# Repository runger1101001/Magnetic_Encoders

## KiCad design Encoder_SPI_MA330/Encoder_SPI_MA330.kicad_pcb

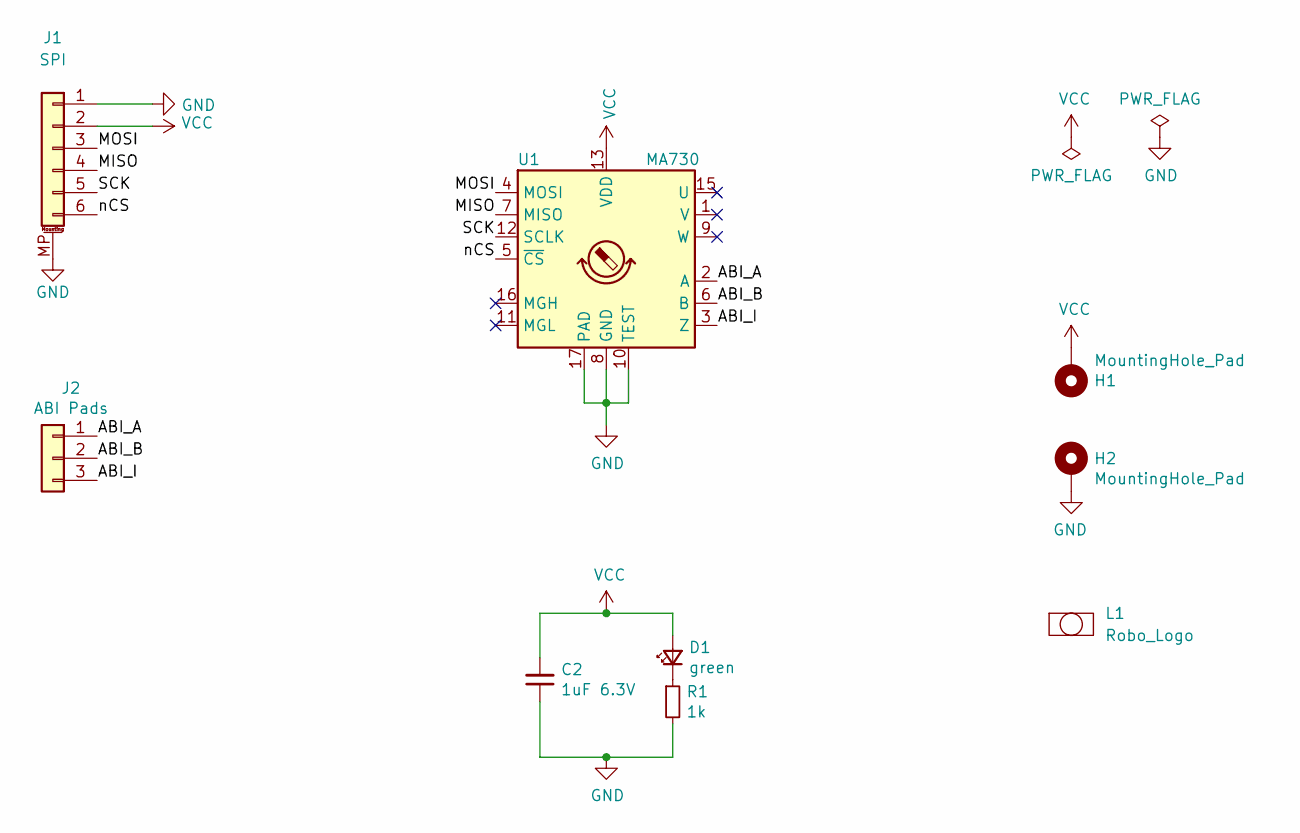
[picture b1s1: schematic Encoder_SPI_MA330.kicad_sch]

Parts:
C2: 1uF 6.3V; C_0402_1005Metric; Part GRT155C80J105KE01D
D1: green; LED_0402_1005Metric; Part 150040VS73240
H1, H2: MountingHole_Pad; MountingHole_2.2mm_M2_ISO7380_Pad
J1: Conn_01x06_MountingPin; JST_SH_SM06B-SRSS-TB_1x06-1MP_P1.00mm_Horizontal; Part Connector_JST:JST_SH_SM06B-SRSS-TB_1x06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
J2: Castellations_ABI; PinHeader_1x03_P2.54mm_Vertical
L1: Robo_Logo; Robo_logo2
R1: 1k; R_0402_1005Metric
U1: MA730; QFN-16-1EP_3x3mm_P0.5mm_EP1.75x1.75mm; Part MA330GQ-Z

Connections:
/ABI_A: J2.1, U1.2 (A)
/ABI_B: J2.2, U1.6 (B)
/ABI_I: J2.3, U1.3 (Z)
/MISO: J1.4, U1.7 (MISO)
/MOSI: J1.3, U1.4 (MOSI)
/SCK: J1.5, U1.12 (SCLK)
/nCS: J1.6, U1.5 (~CS)
GND: C2.1, H2.1, J1.1, J1.MP (MountPin), R1.2, U1.8 (GND), U1.10 (TEST), U1.17 (PAD)
unnamed: D1.1 (K), R1.1
VCC: C2.2, D1.2 (A), H1.1, J1.2, U1.13 (VDD)

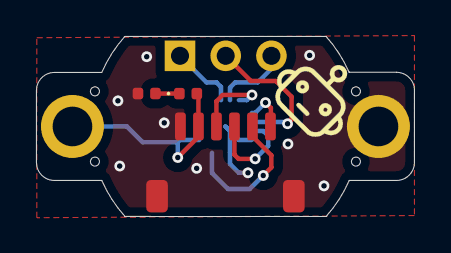
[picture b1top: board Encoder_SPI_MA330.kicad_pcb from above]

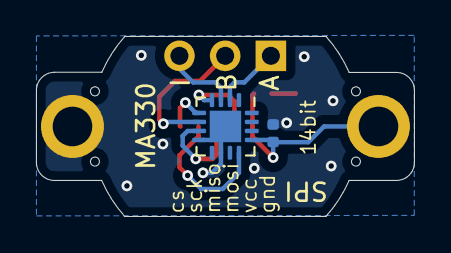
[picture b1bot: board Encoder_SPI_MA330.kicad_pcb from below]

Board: 2 copper layers, 21.0 x 10.0 mm, 13 parts (2 on the bottom side), 10 nets.

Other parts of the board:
H**: Mousebite
H**#2, H**#3, H**#4: Mousebite

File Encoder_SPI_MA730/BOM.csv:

"Item","Ref Des","Qty","Manufacturer","Mfg Part #","Description / Value","Package","Type","Your Instructions / Notes"
"1","C2","1","Generic","Generic","1uF 6.3V","C_0402_1005Metric","?","; Unpolarized capacitor; "
"2","D1","1","Wurth","150040VS73240","green","LED_0402_1005Metric","?","; Light emitting diode; "
"3","H2,H1","2","","Mounting Hole with connection","MountingHole_Pad","MountingHole_2.2mm_M2_ISO7380_Pad","?","; Mounting Hole with connection; "
"4","J1","1","JST","SH_SM08B-SRSS-TB_1x08-1MP_P1.00mm_Horizontal","Conn_01x06_MountingPin","JST_SH_SM08B-SRSS-TB_1x08-1MP_P1.00mm_Horizontal","?","; Generic connectable mounting pin connector, single row, 01x08, script generated (kicad-library-utils/schlib/autogen/connector/); "
"5","J2","1","","Generic connector, single row, 01x04, script generated (kicad-library-utils/schlib/autogen/connector/)","Castellations_ABI","PinHeader_1x04_P2.54mm_Vertical","?","; Generic connector, single row, 01x04, script generated (kicad-library-utils/schlib/autogen/connector/); "
"6","R1","1","","Resistor","1k","R_0402_1005Metric","?","; Resistor; "
"7","U1","1","","Magnetic rotary angle sensor, 14-bit, SPI interface, ABZ, PWM, QFN-16","MA730","QFN-16-1EP_3x3mm_P0.5mm_EP1.75x1.75mm","?","; Magnetic rotary angle sensor, 14-bit, SPI interface, ABZ, PWM, QFN-16; https://www.monolithicpower.com/pub/media/document/m/a/ma730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"

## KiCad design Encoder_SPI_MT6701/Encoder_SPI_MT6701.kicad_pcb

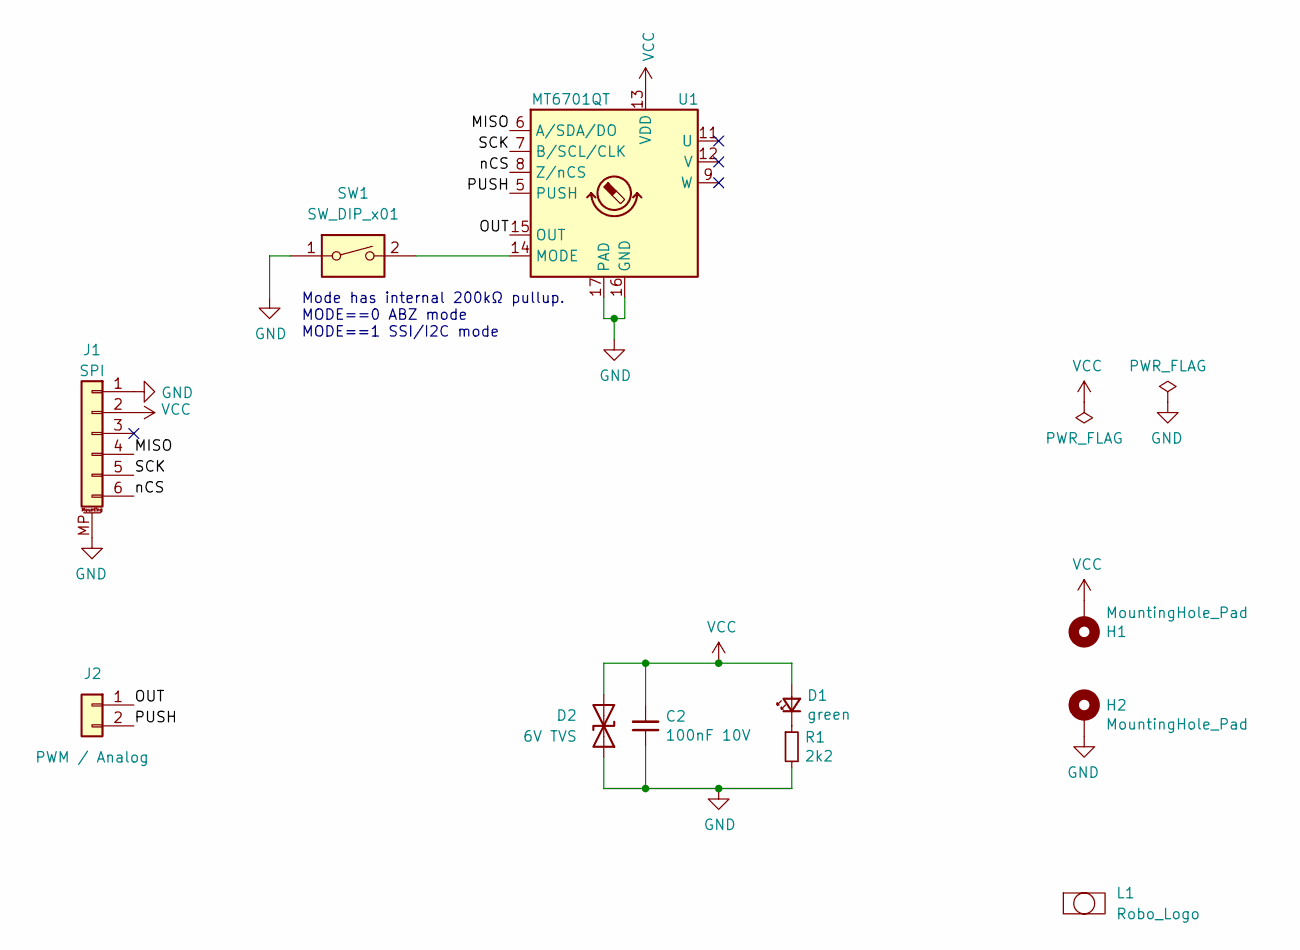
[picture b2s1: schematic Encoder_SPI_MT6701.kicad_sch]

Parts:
C2: 100nF 10V; C_0402_1005Metric; Part GRM155R71A104KA01J
D1: green; LED_0402_1005Metric; Part 150040VS73240
D2: 6V TVS; D_0201_0603Metric; Part SP1005-01WTG
H1, H2: MountingHole_Pad; MountingHole_2.2mm_M2_ISO7380_Pad
J1: Conn_01x06_MountingPin; JST_SH_SM06B-SRSS-TB_1x06-1MP_P1.00mm_Horizontal; Part SCT-WR-S-06P
J2: Conn_01x02; PinHeader_1x02_P2.54mm_Vertical
L1: Robo_Logo; Robo_logo2
R1: 2k2; R_0402_1005Metric; Part Generic 2k2 Resistor
SW1: SW_DIP_x01; SW_DIP_SPSTx01_Slide_Copal_CHS-01B_W7.62mm_P1.27mm; Part THS101
U1: MT6701QT; QFN-16-1EP_3x3mm_P0.5mm_EP1.75x1.75mm; Part MT6701QT-STD

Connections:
/MISO: J1.4, U1.6 (A/SDA/DO)
/OUT: J2.1, U1.15 (OUT)
/PUSH: J2.2, U1.5 (PUSH)
/SCK: J1.5, U1.7 (B/SCL/CLK)
/nCS: J1.6, U1.8 (Z/nCS)
GND: C2.1, D2.1 (A1), H2.1, J1.1, J1.MP (MountPin), R1.2, SW1.1, U1.16 (GND), U1.17 (PAD)
unnamed: D1.1 (K), R1.1
unnamed: SW1.2, U1.14 (MODE)
VCC: C2.2, D1.2 (A), D2.2 (A2), H1.1, J1.2, U1.13 (VDD)

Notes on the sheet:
Mode has internal 200kΩ pullup. MODE==0 ABZ mode MODE==1 SSI/I2C mode

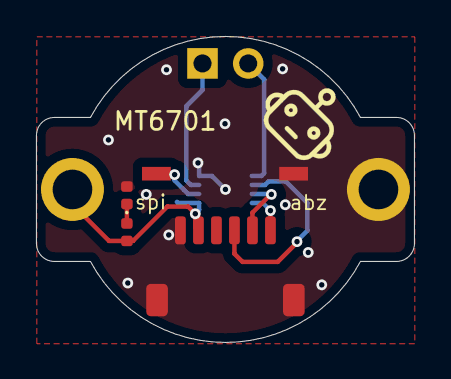
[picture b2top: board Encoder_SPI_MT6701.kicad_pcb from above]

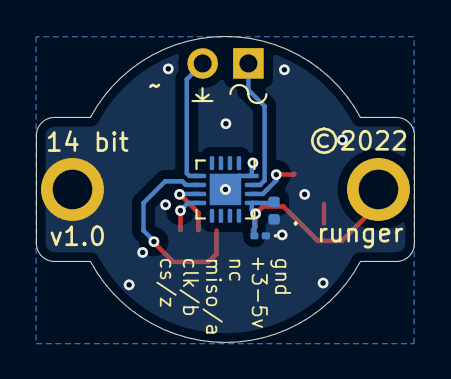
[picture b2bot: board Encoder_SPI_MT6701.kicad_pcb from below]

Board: 2 copper layers, 21.0 x 17.0 mm, 11 parts (3 on the bottom side), 9 nets.

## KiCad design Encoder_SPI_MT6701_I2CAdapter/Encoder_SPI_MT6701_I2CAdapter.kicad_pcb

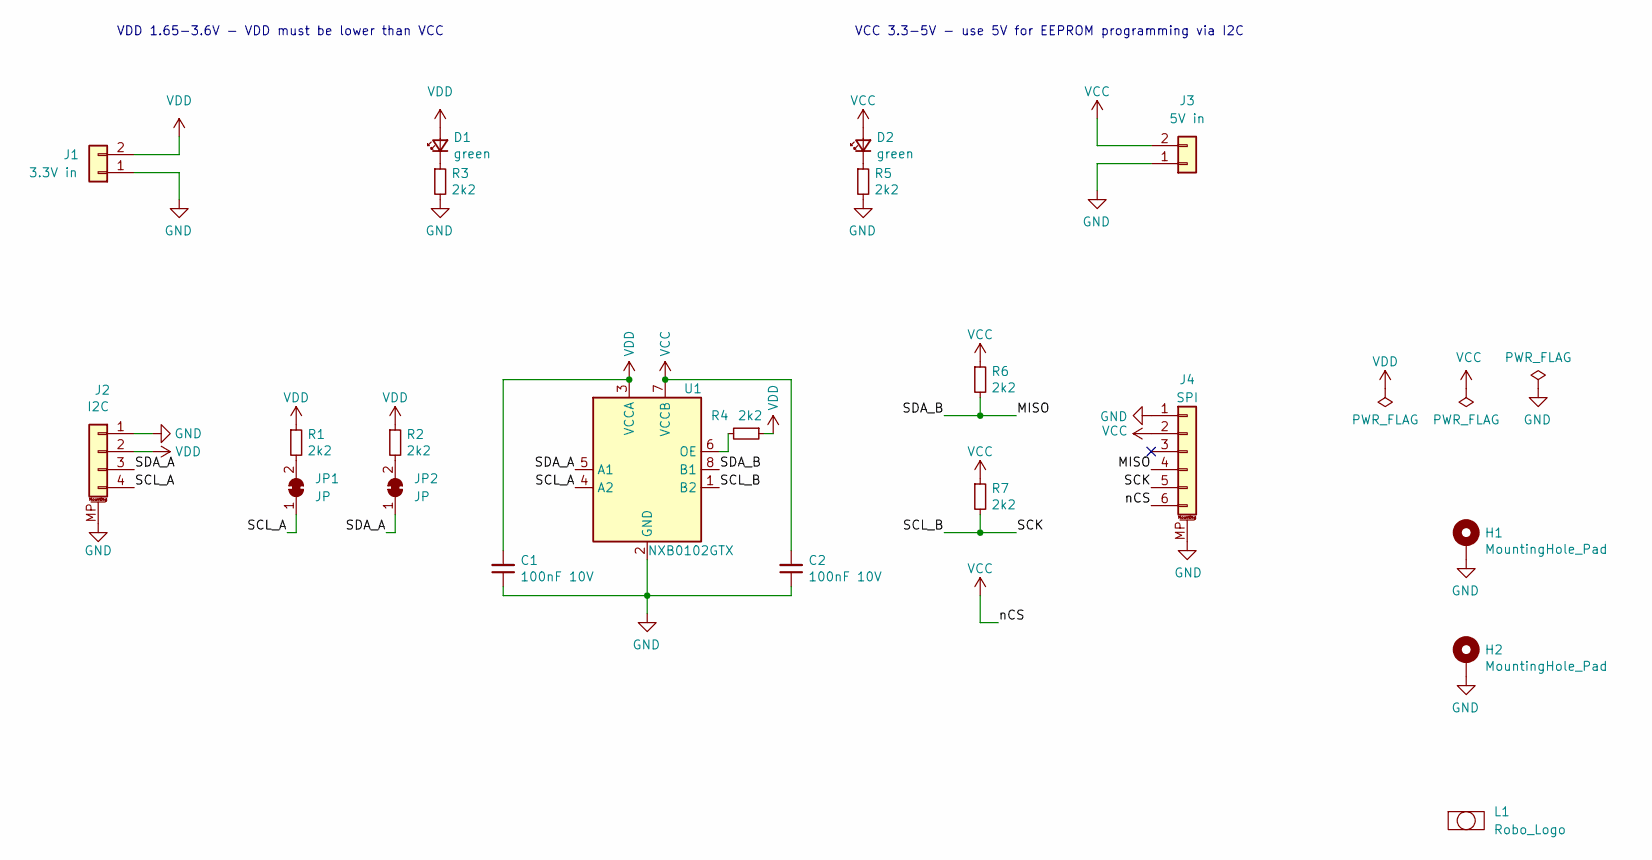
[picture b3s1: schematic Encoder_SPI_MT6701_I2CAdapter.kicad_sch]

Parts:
C1, C2: 100nF 10V; C_0402_1005Metric; Part GRM155R71A104KA01J
D1, D2: green; LED_0402_1005Metric; Part 150040VS73240
H1, H2: MountingHole_Pad; MountingHole_2.2mm_M2_ISO7380_Pad
J1: 3.3V in; PinHeader_1x02_P2.54mm_Vertical
J2: JST_SH_SM04B; JST_SH_SM04B-SRSS-TB_1x04-1MP_P1.00mm_Horizontal; Part SH_SM04B-SRSS-TB_1x04-1MP
J3: 5V in; PinHeader_1x02_P2.54mm_Vertical
J4: JST_SH_SM06B; JST_SH_SM06B-SRSS-TB_1x06-1MP_P1.00mm_Horizontal; Part SH_SM06B-SRSS-TB_1x06-1MP
JP1, JP2: JP; SolderJumper-2_P1.3mm_Bridged2Bar_RoundedPad1.0x1.5mm
L1: Robo_Logo; Robo_logo2
R1, R2, R3, R4, R5, R6, R7: 2k2; R_0402_1005Metric; Part Generic 2k2 Resistor
U1: NXB0102GTX; SOT833-1 (XSON8); Part NXB0102GTX

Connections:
/MISO: J4.4, R6.2, U1.8 (B1)
/SCK: J4.5, R7.2, U1.1 (B2)
/SCL_A: J2.4, JP1.1 (A), U1.4 (A2)
/SDA_A: J2.3, JP2.1 (A), U1.5 (A1)
GND: C1.1, C2.1, H1.1, H2.1, J1.1, J2.1, J2.MP (MountPin), J3.1, J4.1, J4.MP (MountPin), R3.2, R5.2, U1.2 (GND)
unnamed: D1.1 (K), R3.1
unnamed: D2.1 (K), R5.1
unnamed: JP1.2 (B), R1.2
unnamed: JP2.2 (B), R2.2
unnamed: R4.2, U1.6 (OE)
VCC: C2.2, D2.2 (A), J3.2, J4.2, J4.6, R6.1, R7.1, U1.7 (VCCB)
VDD: C1.2, D1.2 (A), J1.2, J2.2, R1.1, R2.1, R4.1, U1.3 (VCCA)

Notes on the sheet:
VDD 1.65-3.6V - VDD must be lower than VCC
VCC 3.3-5V - use 5V for EEPROM programming via I2C

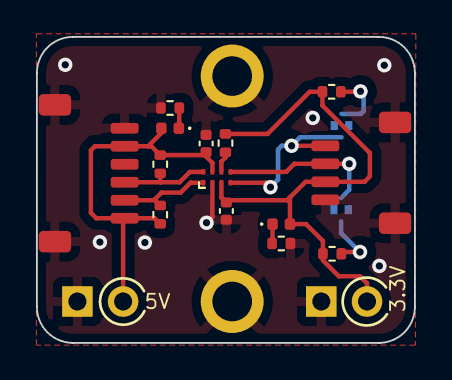
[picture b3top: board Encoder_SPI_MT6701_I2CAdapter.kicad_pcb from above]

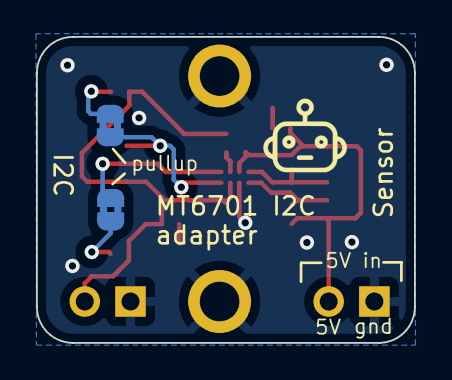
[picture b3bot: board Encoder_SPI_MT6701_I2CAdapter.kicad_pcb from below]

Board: 2 copper layers, 21.0 x 17.0 mm, 21 parts (3 on the bottom side), 12 nets.

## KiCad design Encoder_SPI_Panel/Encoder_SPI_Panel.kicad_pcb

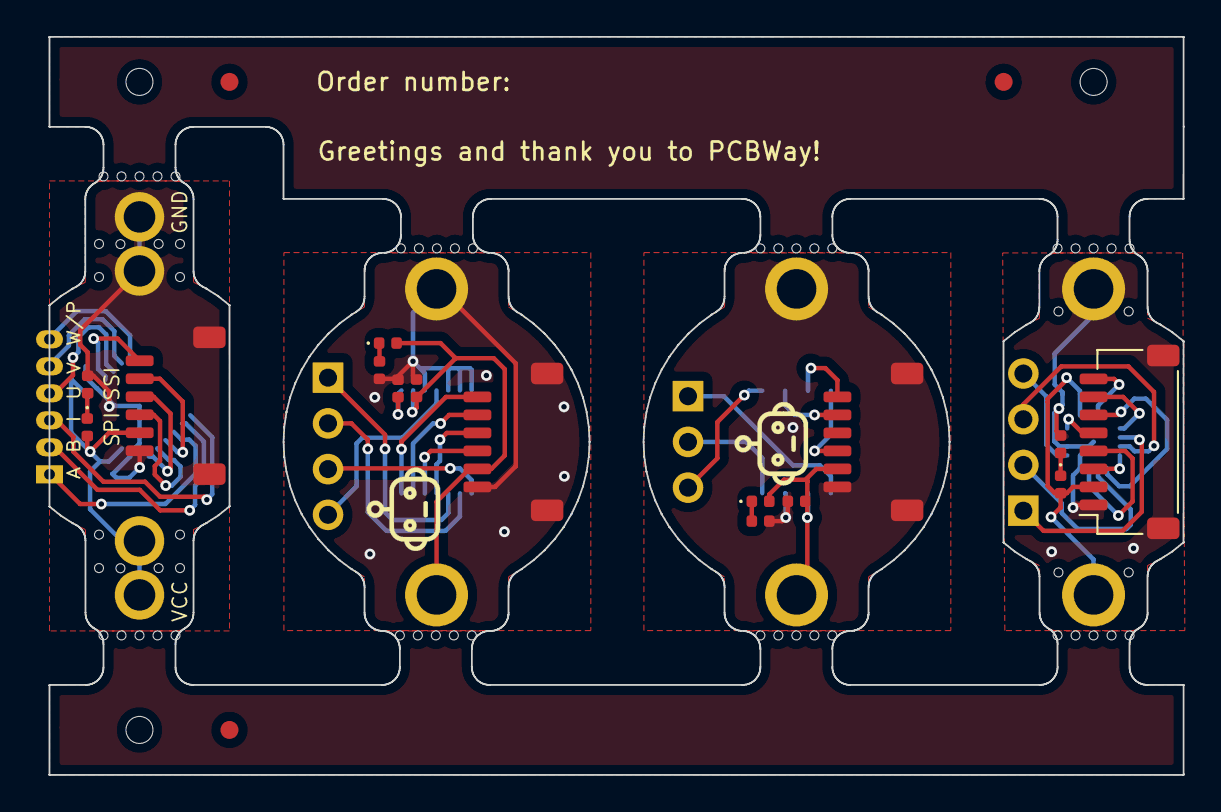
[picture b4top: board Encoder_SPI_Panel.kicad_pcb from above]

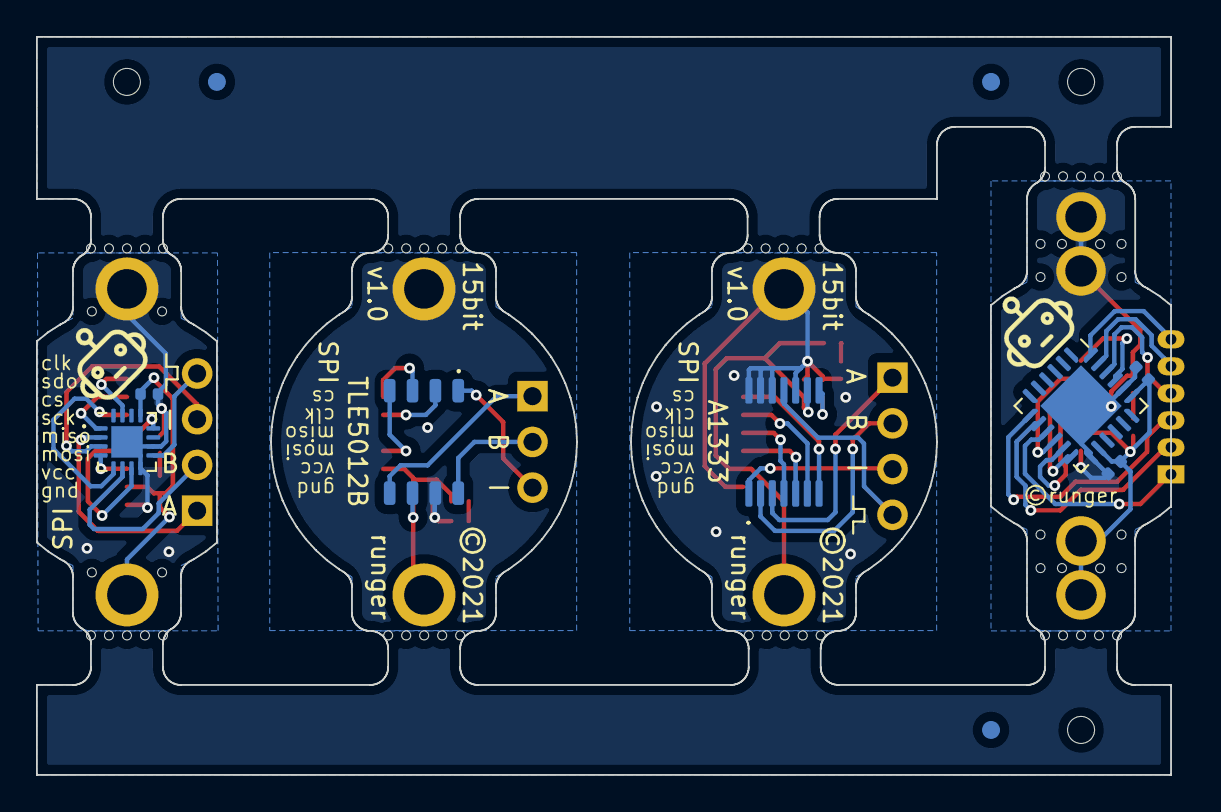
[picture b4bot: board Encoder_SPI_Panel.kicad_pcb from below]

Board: 2 copper layers, 63.0 x 41.0 mm, 56 parts (9 on the bottom side), 47 nets.

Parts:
B1-C1, B2-C1, B2-C2, B3-C2: 100nF 6.3V; C_0402_1005Metric
B1-C2: 10uF 6.3V; C_0402_1005Metric
B1-D1, B2-D1, B3-D1, B4-D1: green; LED_0402_1005Metric
B1-G***, B4-G***: LOGO; Robo_logo2
B1-H1, B1-H1#2, B1-H2, B1-H2#2: MountingHole_Pad; MountingHole_Pad_1.75mm_2.75mm
B1-H**, B1-H**#2, B1-H**#3, B1-H**#4, B1-H**#5, B1-H**#6, B1-H**#7, B1-H**#8, B1-H**#9, B1-H**#10, B1-H**#11, B1-H**#12, B4-H**, B4-H**#2, B4-H**#3, B4-H**#4: Mousebite
B1-J1, B2-J1, B3-J1: Conn_01x06_MountingPin; JST_SH_SM06B-SRSS-TB_1x06-1MP_P1.00mm_Horizontal
B1-J2: Castellations_SPI; Castellations_x6_1.5p_1hole
B1-R1, B2-R1, B3-R1, B4-R1: 1k; R_0402_1005Metric
B1-U1: AEAT_8800_Q24; QFN-24-1EP_5x5mm_P0.65mm_EP3.2x3.2mm
B2-G***, B3-G***: LOGO; Robo_logo
B2-H1, B2-H2, B3-H1, B3-H2, B4-H1, B4-H2: MountingHole_Pad; MountingHole_2.2mm_M2_ISO7380_Pad
B2-J2, B4-J2: Castellations_ABI; PinHeader_1x04_P2.54mm_Vertical
B2-U1: A1333; TSSOP-14_4.4x5mm_P0.65mm
B3-J2: Castellations_ABI; PinHeader_1x03_P2.54mm_Vertical
B3-U1: TLE5012B; Infineon_PG-DSO-8
B4-C2: 1uF 6.3V; C_0402_1005Metric
B4-J1: Conn_01x06_MountingPin; JST_SH_SM08B-SRSS-TB_1x08-1MP_P1.00mm_Horizontal
B4-U1: MA730; QFN-16-1EP_3x3mm_P0.5mm_EP1.75x1.75mm

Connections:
B1-ABI_A: B1-J2.1, B1-U1.9
B1-ABI_B: B1-J2.2, B1-U1.8
B1-ABI_I: B1-J2.3, B1-U1.7
B1-GND: B1-C1.2, B1-C2.1, B1-H2.1, B1-H2#2.1, B1-J1.1, B1-J1.MP, B1-R1.2, B1-U1.13, B1-U1.20, B1-U1.25
B1-MISO: B1-J1.4, B1-U1.12
B1-MOSI: B1-J1.3, B1-U1.11
B1-Net-(D1-Pad1): B1-D1.1, B1-R1.1
B1-SCK: B1-J1.5, B1-U1.10
B1-UVW_U: B1-J2.4, B1-U1.22
B1-UVW_V: B1-J2.5, B1-U1.23
B1-UVW_W-PWM: B1-J2.6, B1-U1.24
B1-VCC: B1-C1.1, B1-C2.2, B1-D1.2, B1-H1.1, B1-H1#2.1, B1-J1.2, B1-U1.14, B1-U1.19
B1-nCS: B1-J1.6, B1-U1.21
B2-ABI_A: B2-J2.1, B2-U1.10
B2-ABI_B: B2-J2.2, B2-U1.9
B2-ABI_I: B2-J2.3, B2-U1.8
B2-GND: B2-C1.2, B2-C2.1, B2-H2.1, B2-J1.1, B2-J1.MP, B2-R1.2, B2-U1.3, B2-U1.5, B2-U1.6, B2-U1.7
B2-MISO: B2-J1.4, B2-U1.11
B2-MOSI: B2-J1.3, B2-U1.12
B2-Net-(C1-Pad1): B2-C1.1, B2-U1.1
B2-Net-(D1-Pad1): B2-D1.1, B2-R1.1
B2-PWM: B2-J2.4, B2-U1.4
B2-SCK: B2-J1.5, B2-U1.13
B2-VCC: B2-C2.2, B2-D1.2, B2-H1.1, B2-J1.2, B2-U1.2
B2-nCS: B2-J1.6, B2-U1.14
B3-ABI_A: B3-J2.1, B3-U1.5
B3-ABI_B: B3-J2.2, B3-U1.8
B3-ABI_I: B3-J2.3, B3-U1.1
B3-GND: B3-C2.1, B3-H2.1, B3-J1.1, B3-J1.MP, B3-R1.2, B3-U1.7
B3-MOSI: B3-J1.3, B3-U1.4
B3-Net-(D1-Pad1): B3-D1.1, B3-R1.1
B3-SCK: B3-J1.5, B3-U1.2
B3-VCC: B3-C2.2, B3-D1.2, B3-H1.1, B3-J1.2, B3-U1.6
B3-nCS: B3-J1.6, B3-U1.3
B4-ABI_A: B4-J2.1, B4-U1.2
B4-ABI_B: B4-J2.2, B4-U1.6
B4-ABI_I: B4-J2.3, B4-U1.3
B4-GND: B4-C2.1, B4-H2.1, B4-J1.1, B4-J1.MP, B4-R1.2, B4-U1.8, B4-U1.10, B4-U1.17
B4-MISO: B4-J1.4, B4-U1.7
B4-MOSI: B4-J1.3, B4-U1.4
B4-Net-(D1-Pad1): B4-D1.1, B4-R1.1
B4-PWM: B4-J2.4, B4-U1.9
B4-SCK: B4-J1.5, B4-U1.12
B4-SSCK: B4-J1.8, B4-U1.15
B4-SSD: B4-J1.7, B4-U1.1
B4-VCC: B4-C2.2, B4-D1.2, B4-H1.1, B4-J1.2, B4-U1.13
B4-nCS: B4-J1.6, B4-U1.5

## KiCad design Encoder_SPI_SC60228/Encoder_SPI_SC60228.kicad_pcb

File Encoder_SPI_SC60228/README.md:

# SC60228 magnetic angle sensor

Small (21x17mm) board for the SC60228 magnetic absolute angle sensor.

For use in motor control or robotics applications, the sensor measures the orientation (angle in the plane) of a nearby diametrically magnetized magnet.

That sounds more complicated than using it really is, so lets describe it another way:
- attach the magnet to the axis of something that rotates
- put the sensor near it
- read angles with your Arduino

| Back of board | Front of board |
| --- | --- |
| with SH 1.0 connector  | with sensor  |

## Features

- 3V to 5V operation
- 12 bit accuracy, 4096 positions per revolution 
- SPI interface up to 10MHz
- power indication LED (green, dim)

Datasheet of the sensor: http://www.semiment.com/download?filePath=product/fuCDPH4YG3usSN69gqmqQ3rSuHEqBBjj6cn1mMuu.pdf&fileName=SC60228_EN-VA1.0.pdf

## Getting one

You may be able to buy some here:

Or you could make one - it is open source, you will find gerber files and BOM in the repo, and design files for KiCad 6.

## Usage

The sensor has to be precisely positioned near the magnet. The magnet should be precisely on-axis and in-plane (no wobble!). The sensor should be mounted with an air-gap of about 0.5mm to the magnet.

Taking the time to mount the magnet and sensor board carefully will improve the accuracy and smoothness of your readings.

The sensor has an SPI interface:

The SPI interface is available on a JST-SH 6-pin socket. Pre-made cables are available cheaply on AliExpress and other sources.

You may connect VCC to either 3.3V or 5V. 

Connect the other lines (MOSI, MISO, CLK and CS) to the respective counterparts on your MCU board.

Note: The sensor board does not pull the CS line up.

## Communications

SPI interface:
- SPI Mode 1
- MSB first
- max 10MHz SPI clock

See [datasheet](http://www.semiment.com/download?filePath=product/fuCDPH4YG3usSN69gqmqQ3rSuHEqBBjj6cn1mMuu.pdf&fileName=SC60228_EN-VA1.0.pdf) for details, or use an existing software driver.

:warning: Note: cable length, shielding (or lack thereof) and environmental noise may limit performance to significantly less than the 10MHz maximum.

## Software

The sensor can be used with any appropriate SPI driver.

The author uses it with Arduino-compatible MCU boards and the [SimpleFOC library](http://www.simplefoc.com).

A driver for the sensor for Arduino and SimpleFOC can be found here: [SimpleFOC drivers library](https://github.com/simplefoc/Arduino-FOC-drivers/tree/master/src/encoders/sc60228)

## Physical dimensions

v1.0: 21 x 17 x 4mm (1.6mm PCB)

## Cables

Pre-made JST SH 1.0 cables are available. When buying cables with two plugs, choose the type that is called "reverse connection" - where the pins on both ends of the cable have the same order.

Some links to compatible cables / breakout boards:

 - https://www.tindie.com/products/26431/
 - https://www.aliexpress.com/item/4000421829259.html
 - https://www.aliexpress.com/item/4001235017139.html
 - https://www.pololu.com/product/4770
 - https://www.pololu.com/product/4772

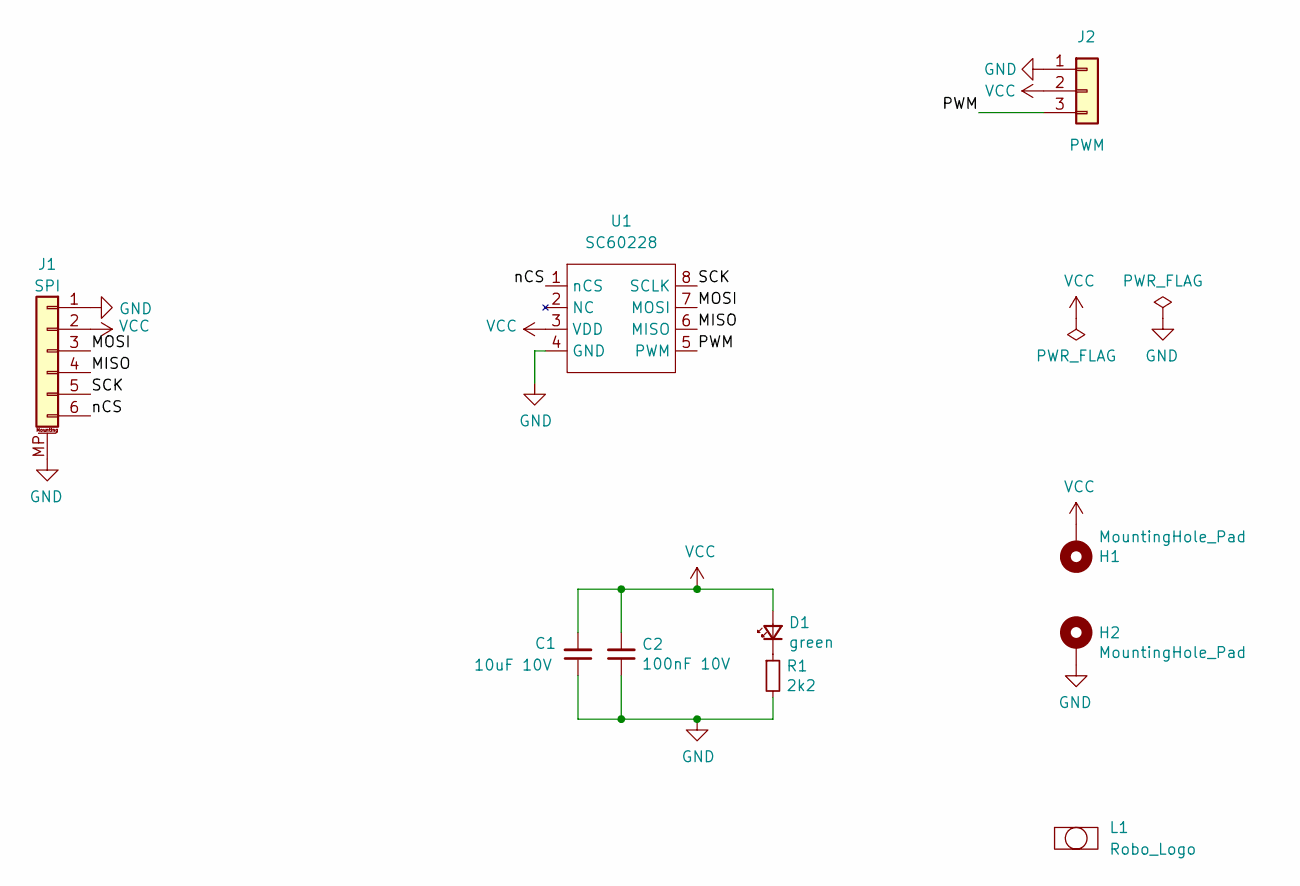
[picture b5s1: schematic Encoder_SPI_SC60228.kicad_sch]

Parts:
C1: 10uF 10V; C_0402_1005Metric; Part GRM155R61A106ME11D
C2: 100nF 10V; C_0402_1005Metric; Part GRM155R71A104KA01J
D1: green; LED_0402_1005Metric; Part 150040VS73240
H1, H2: MountingHole_Pad; MountingHole_2.2mm_M2_ISO7380_Pad
J1: Conn_01x06_MountingPin; JST_SH_SM06B-SRSS-TB_1x06-1MP_P1.00mm_Horizontal; Part SCT-WR-S-06P
J2: Conn_01x03; PinHeader_1x03_P2.54mm_Vertical
L1: Robo_Logo; Robo_logo2
R1: 2k2; R_0402_1005Metric; Part Generic 2k2 Resistor
U1: SC60228; SOP-8_3.9x4.9mm_P1.27mm; Part SC60228

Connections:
/MISO: J1.4, U1.6 (MISO)
/MOSI: J1.3, U1.7 (MOSI)
/PWM: J2.3, U1.5 (PWM)
/SCK: J1.5, U1.8 (SCLK)
/nCS: J1.6, U1.1 (nCS)
GND: C1.1, C2.1, H2.1, J1.1, J1.MP (MountPin), J2.1, R1.2, U1.4 (GND)
unnamed: D1.1 (K), R1.1
VCC: C1.2, C2.2, D1.2 (A), H1.1, J1.2, J2.2, U1.3 (VDD)

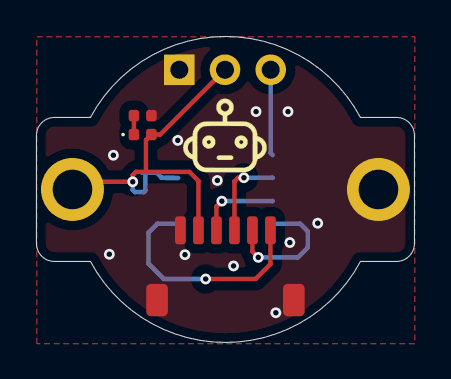
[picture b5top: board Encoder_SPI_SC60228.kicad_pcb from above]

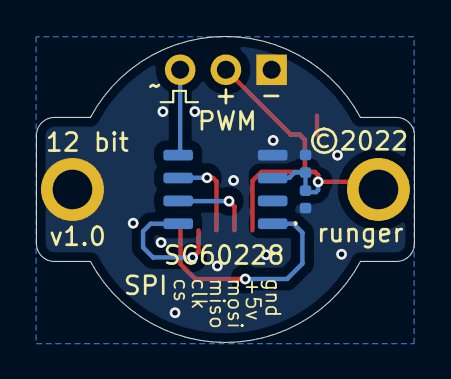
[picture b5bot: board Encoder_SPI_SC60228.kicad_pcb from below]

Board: 2 copper layers, 21.0 x 17.0 mm, 10 parts (3 on the bottom side), 8 nets.

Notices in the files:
Encoder_SPI_MT6701/Encoder_SPI_MT6701.kicad_pcb:
©2022
Encoder_SPI_Panel/Encoder_SPI_Panel.kicad_pcb:
©2021
©runger
